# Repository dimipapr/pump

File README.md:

# IoT Irrigation Control System

This repository contains the product definition and requirements documentation for an IoT system used for remote monitoring, control, and protection of irrigation systems.

## Documentation Structure

- `docs/0.product_definition_and_requirements.md`  
  Main source of truth for product scope, users, requirements, system state, architecture, MVP, and roadmap.

- `docs/1.parking_lot.md`  
  Fast capture space for thoughts, ideas, risks, concerns, reminders, and implementation notes that should not interrupt the current workflow.

- `docs/2.decision_log.md`  
  Records important product, system, architecture, MVP, and implementation decisions.

- `docs/3.open_questions.md`  
  Tracks unresolved questions that must be answered before or during development.

- `docs/assets/diagrams/`  
  Stores diagrams, architecture sketches, state diagrams, and flow diagrams.

- `archive/old_docs/`  
  Stores previous documentation drafts that are no longer the active source of truth.

## Workflow

The main document is the source of truth.

New thoughts should follow this flow:

```text
Idea appears
   ↓
Is it relevant to the current task?
   ├── Yes → handle it now
   └── No → write it in Parking Lot
              ↓
        Continue current task
              ↓
        Review Parking Lot later
              ↓
        Move / classify / discard

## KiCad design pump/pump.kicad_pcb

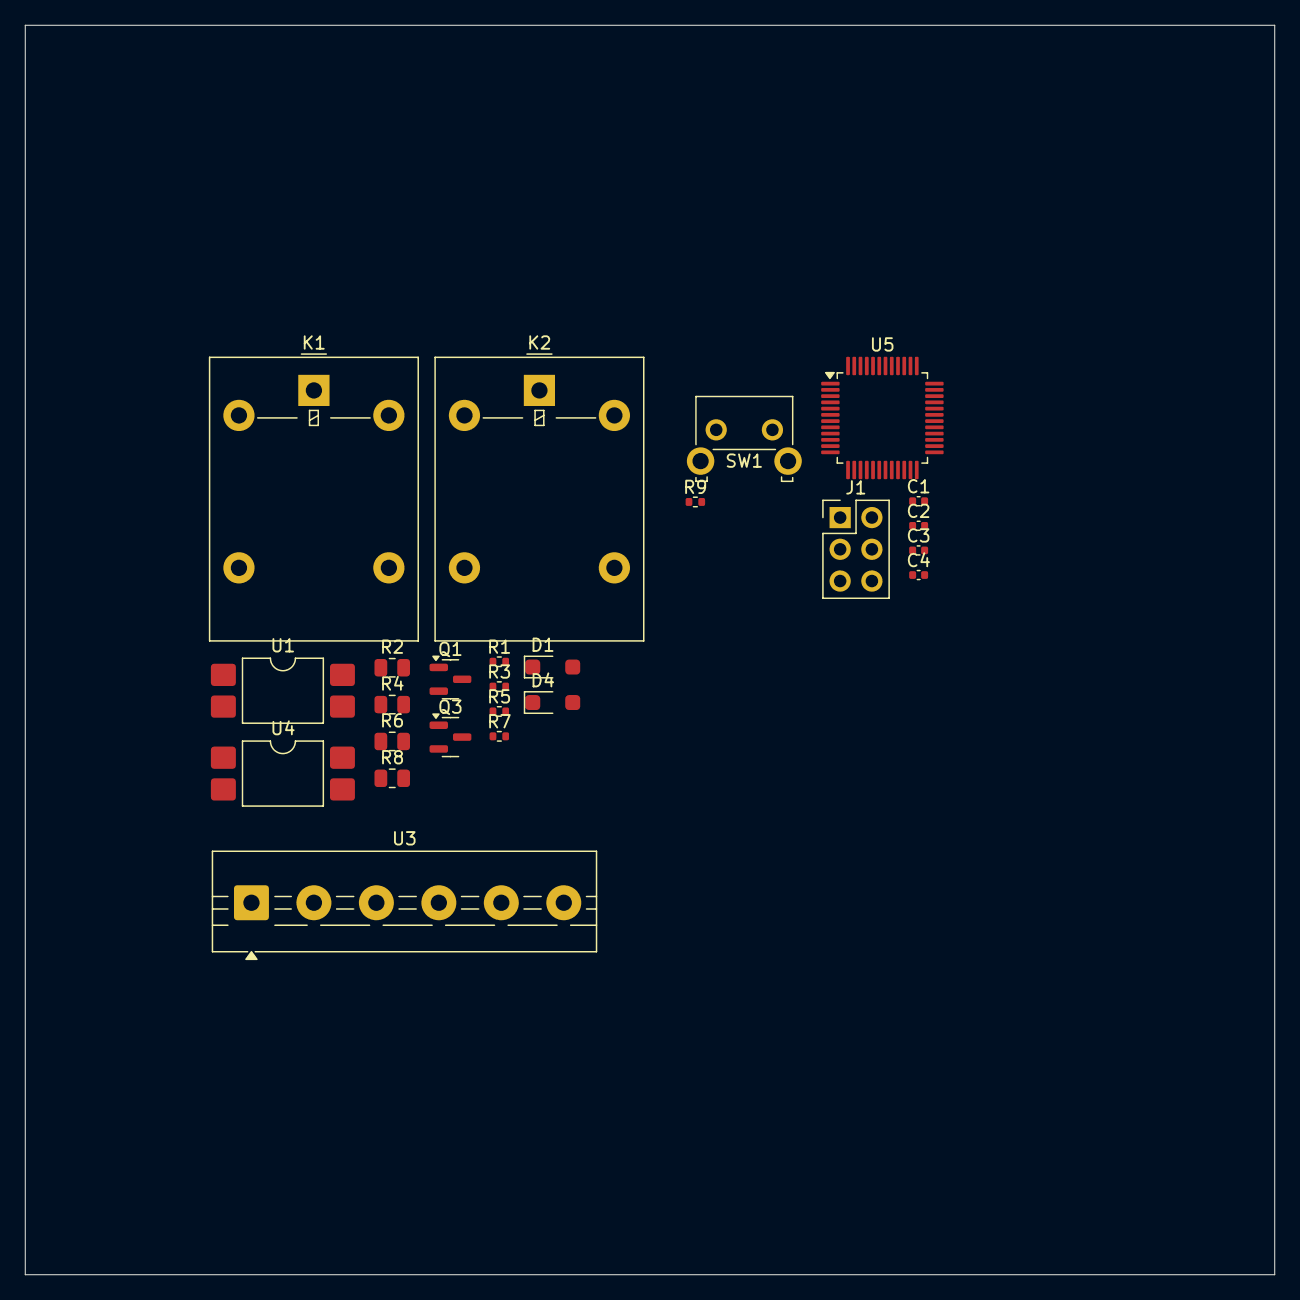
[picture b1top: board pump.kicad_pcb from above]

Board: 2 copper layers, 100.0 x 100.0 mm, 25 parts (0 on the bottom side), 16 nets, no tracks yet.

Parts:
C1, C2, C3, C4: 100n; C_0402_1005Metric
D1, D4: SM4007PL
J1: AVR-UPDI-6; PinHeader_2x03_P2.54mm_Vertical
K1, K2: G5LE-1; Relay_SPDT_Omron-G5LE-1
Q1, Q3: MMBT5401; SOT-23
R1, R3, R5, R7: 20k; R_0402_1005Metric
R2, R6: 220; R_0805_2012Metric
R4, R8: 1k5; R_0805_2012Metric
R9: 330; R_0402_1005Metric
SW1: SW_DPST_x2; SW_Tactile_SKHH_Angled
U1, U4: LTV-817S; SMDIP-4_W9.53mm
U3: 40PC015G; TerminalBlock_MaiXu_MX126-5.0-06P_1x06_P5.00mm
U5: AVR64DA48-I/PT; TQFP-48_7x7mm_P0.5mm

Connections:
+12V: Q1.2 (E), Q3.2 (E), R1.1, R7.1
/ControlRelays/RELAY_START: R2.1, R3.1
/ControlRelays/RELAY_STOP: R5.1, R6.1
/Mcu/UPDI: J1.1 (DATA), U5.41 (UPDI)
/Mcu/VDD: C1.1, C3.1, C4.1, J1.2 (VCC), U5.14 (VDD), U5.28 (AVDD), U5.42 (VDD)
/Mcu/~RESET: C2.1, R9.2, U5.40 (~RESET/PF6)
GND: C1.2, C2.2, C3.2, C4.2, D1.2 (A), D4.2 (A), J1.6 (GND), K1.2, K2.2, R3.2, R5.2, SW1.1 (A), U1.2, U1.3, U3.2 (GND), U4.2, U4.3, U5.15 (GND), U5.29 (GND), U5.43 (GND)
unnamed: D1.1 (K), K2.5, Q1.3 (C)
unnamed: D4.1 (K), K1.5, Q3.3 (C)
unnamed: Q1.1 (B), R8.2
unnamed: Q3.1 (B), R4.2
unnamed: R1.2, R4.1, U4.4
unnamed: R2.2, U4.1
unnamed: R6.2, U1.1
unnamed: R7.2, R8.1, U1.4
unnamed: R9.1, SW1.2 (B)

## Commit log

2025-07-13 hello
2025-07-13 power switching thoughts
2025-07-15 added backup switchover cirquit
2025-07-15 switchover cirquit kinda complete
2025-08-02 lets go
2025-08-03 starting last time
2025-08-03 added system wide block diagram
2025-08-04 Added control relays schematic
2025-08-04 added pressure sensor modulew
2025-08-04 some stuff
2025-08-05 added avr64da64 as mcu and basic decoupling on power pins
2025-08-06 finished control relays schematic and footprints
2025-08-06 finished mcu decoupling and reset cirquit
2025-08-06 added UPDI connector
2025-08-06 added bypass cap in updi line
2025-08-06 Bypass on data line? LOL! Removed updi capacitor
2025-08-06 time to go
2026-04-23 hello there
2026-04-23 concept 1st draft
2026-04-23 added numbering to system functionality
2026-04-23 documents outline and added 4.3 User Data Reliability on prs
2026-04-23 finalized prs
2026-04-23 urd skeleton
2026-04-24 a new last start
2026-04-24 added high level functionality
2026-04-24 added local llm support and review scripts
2026-04-24 locked part 0: document control
2026-04-24 1.2 Product Goal
2026-04-24 cleaner and more accurate description
2026-04-24 removed in-out of scope and populated system functionality
2026-04-24 added target cirquit in scope
2026-04-24 my first decision :D
2026-04-24 populated prompt files
2026-04-24 cleaned up ghosts
2026-04-24 more cleanup
2026-04-24 finaly
2026-04-25 removed llm sheenanigans
2026-04-25 populated user section
2026-04-25 added the no anauthorized user rule
2026-04-25 finalized section 2
2026-04-25 translated 1.4 System Functionality inpo 3. Product requirements
2026-04-25 finalized #3 Product Requirements and cleaned up document
